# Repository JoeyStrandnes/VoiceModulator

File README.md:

# ESP32-S2 Voice Modulator
This is a work in progress ESP32-S2 Voice Modulator 

### Project goals

- [ ] Capture audio from onboard microphone or headsets.
- [ ] Output audio to a phone or computer by emulating an electret microphone.
- [ ] Modify captured audio in "real" time.

## Schematic and analog functionality

##### It is still a work in progress, use with discretion!

### Microphone amplifier

<iframe width="800" height="600" src="https://www.multisim.com/content/QH8fA5JWDjDa823kgBHJLT/electretmic-amplifier/open"></iframe>

### Microphone output

<iframe width="800" height="600" src="https://www.multisim.com/content/xYbAdgF2BNmvYUGru4YRbm/dac_to_electret/open"></iframe>

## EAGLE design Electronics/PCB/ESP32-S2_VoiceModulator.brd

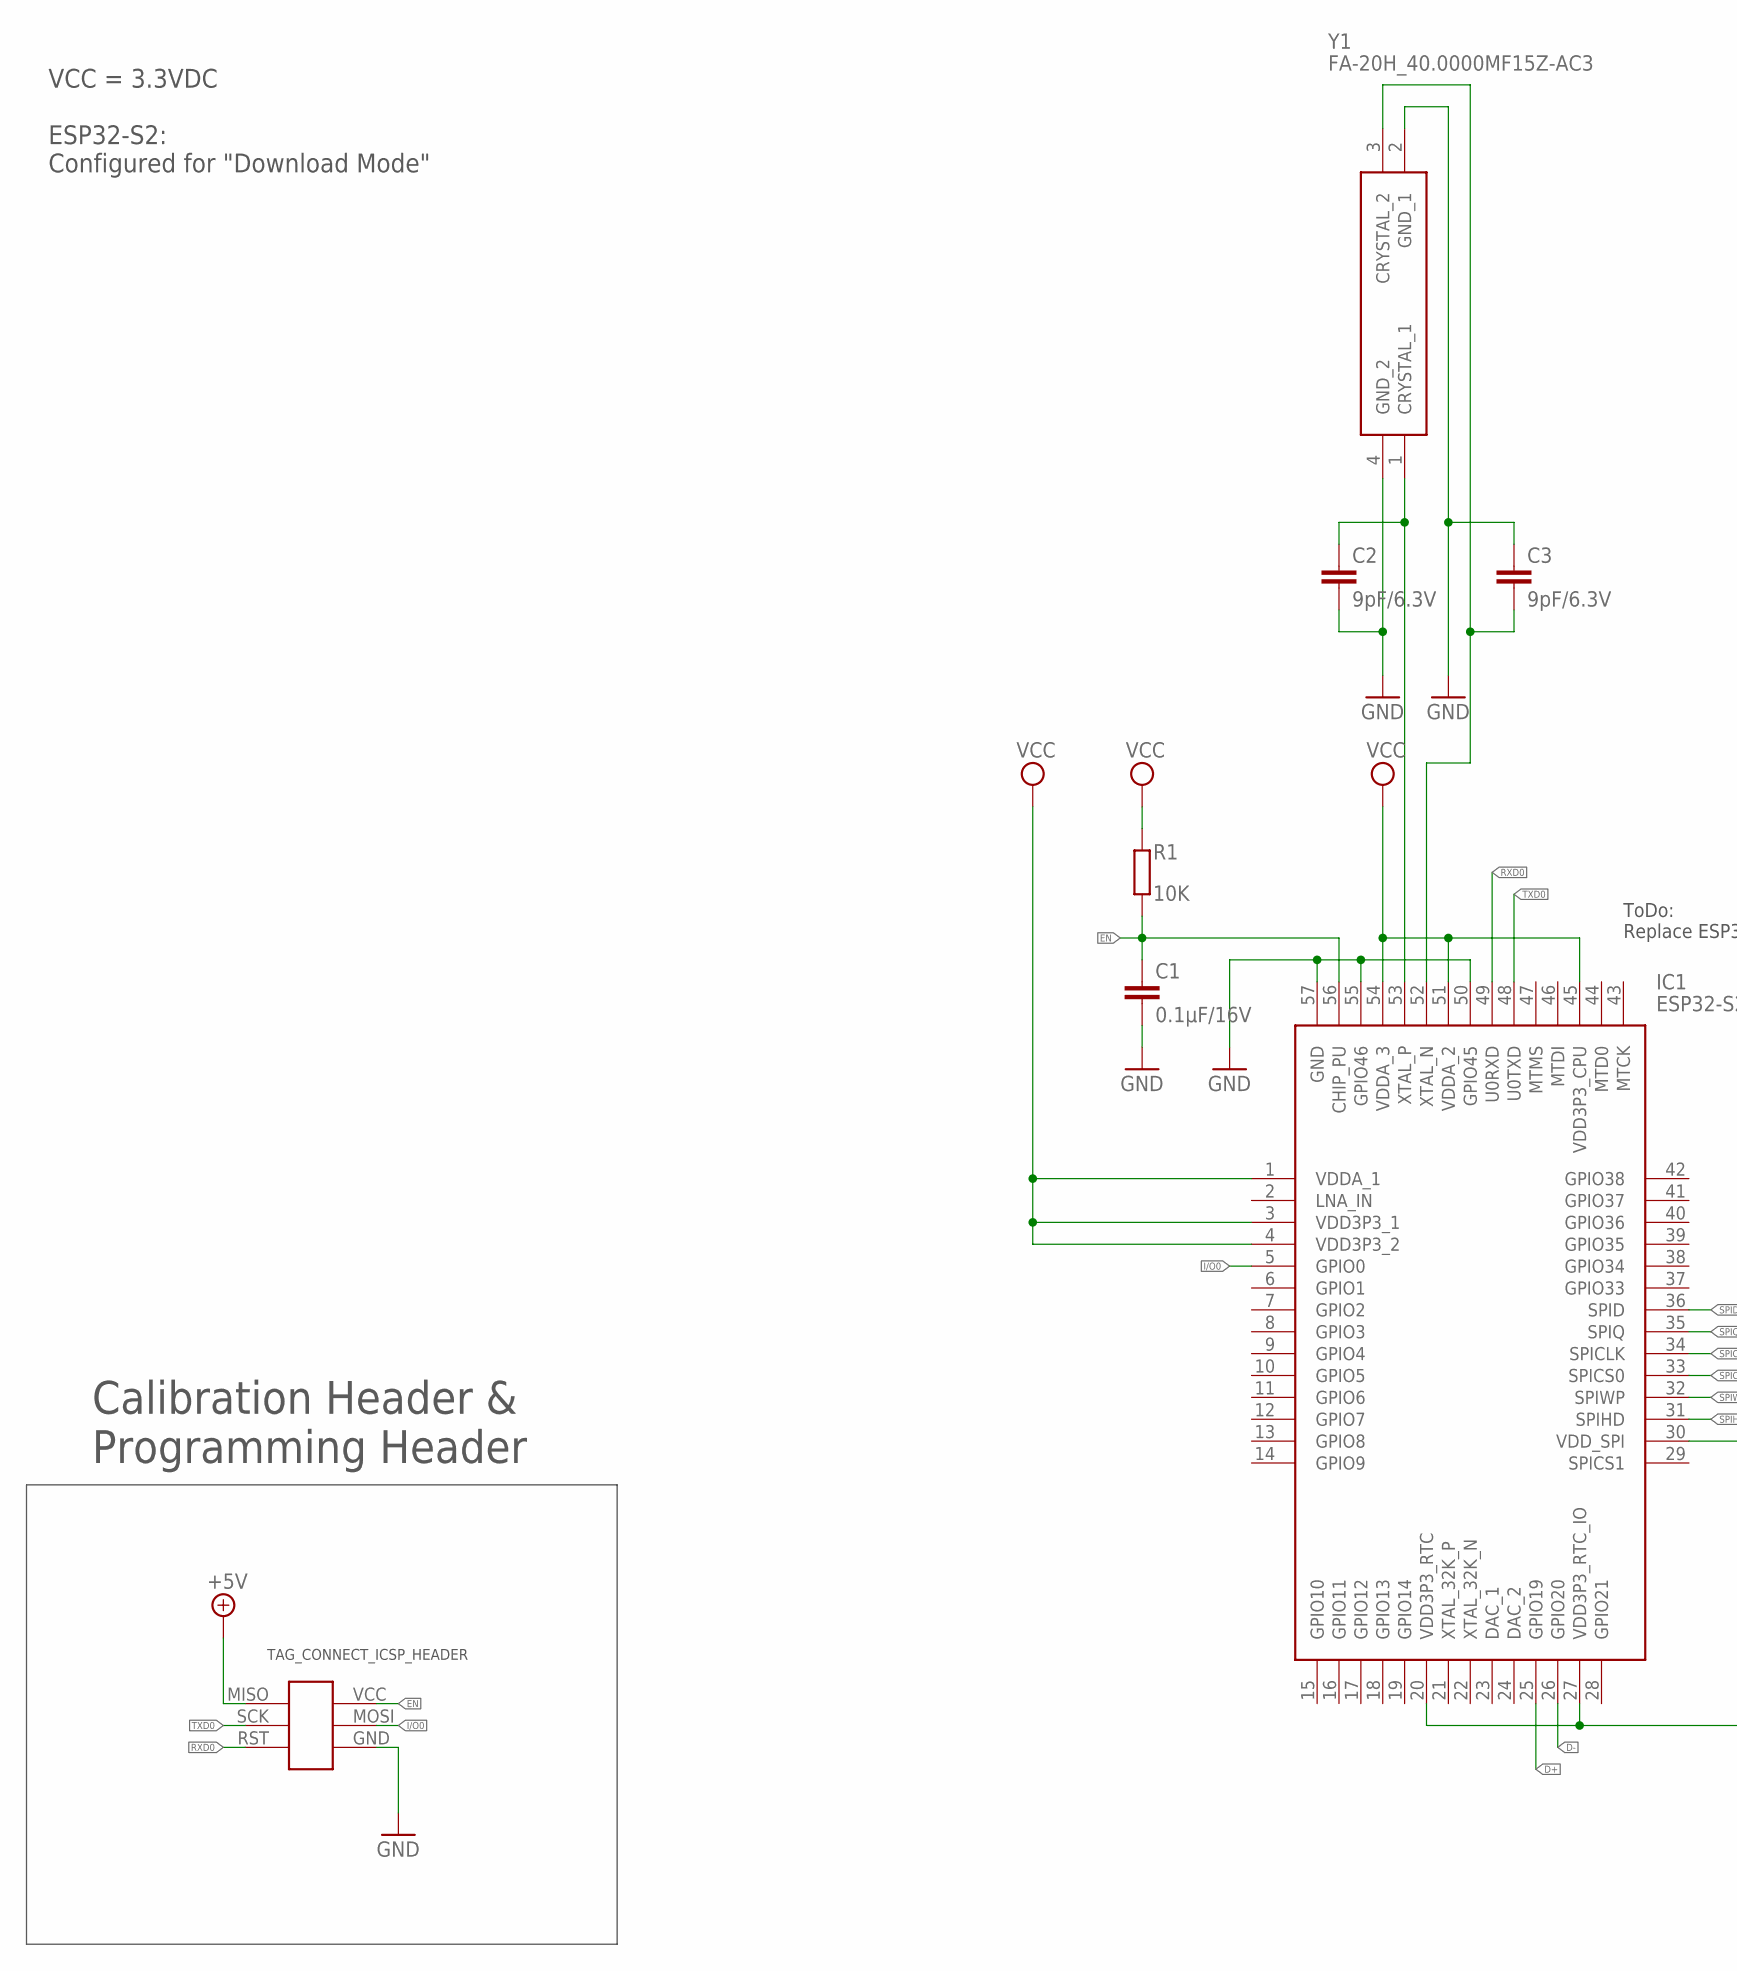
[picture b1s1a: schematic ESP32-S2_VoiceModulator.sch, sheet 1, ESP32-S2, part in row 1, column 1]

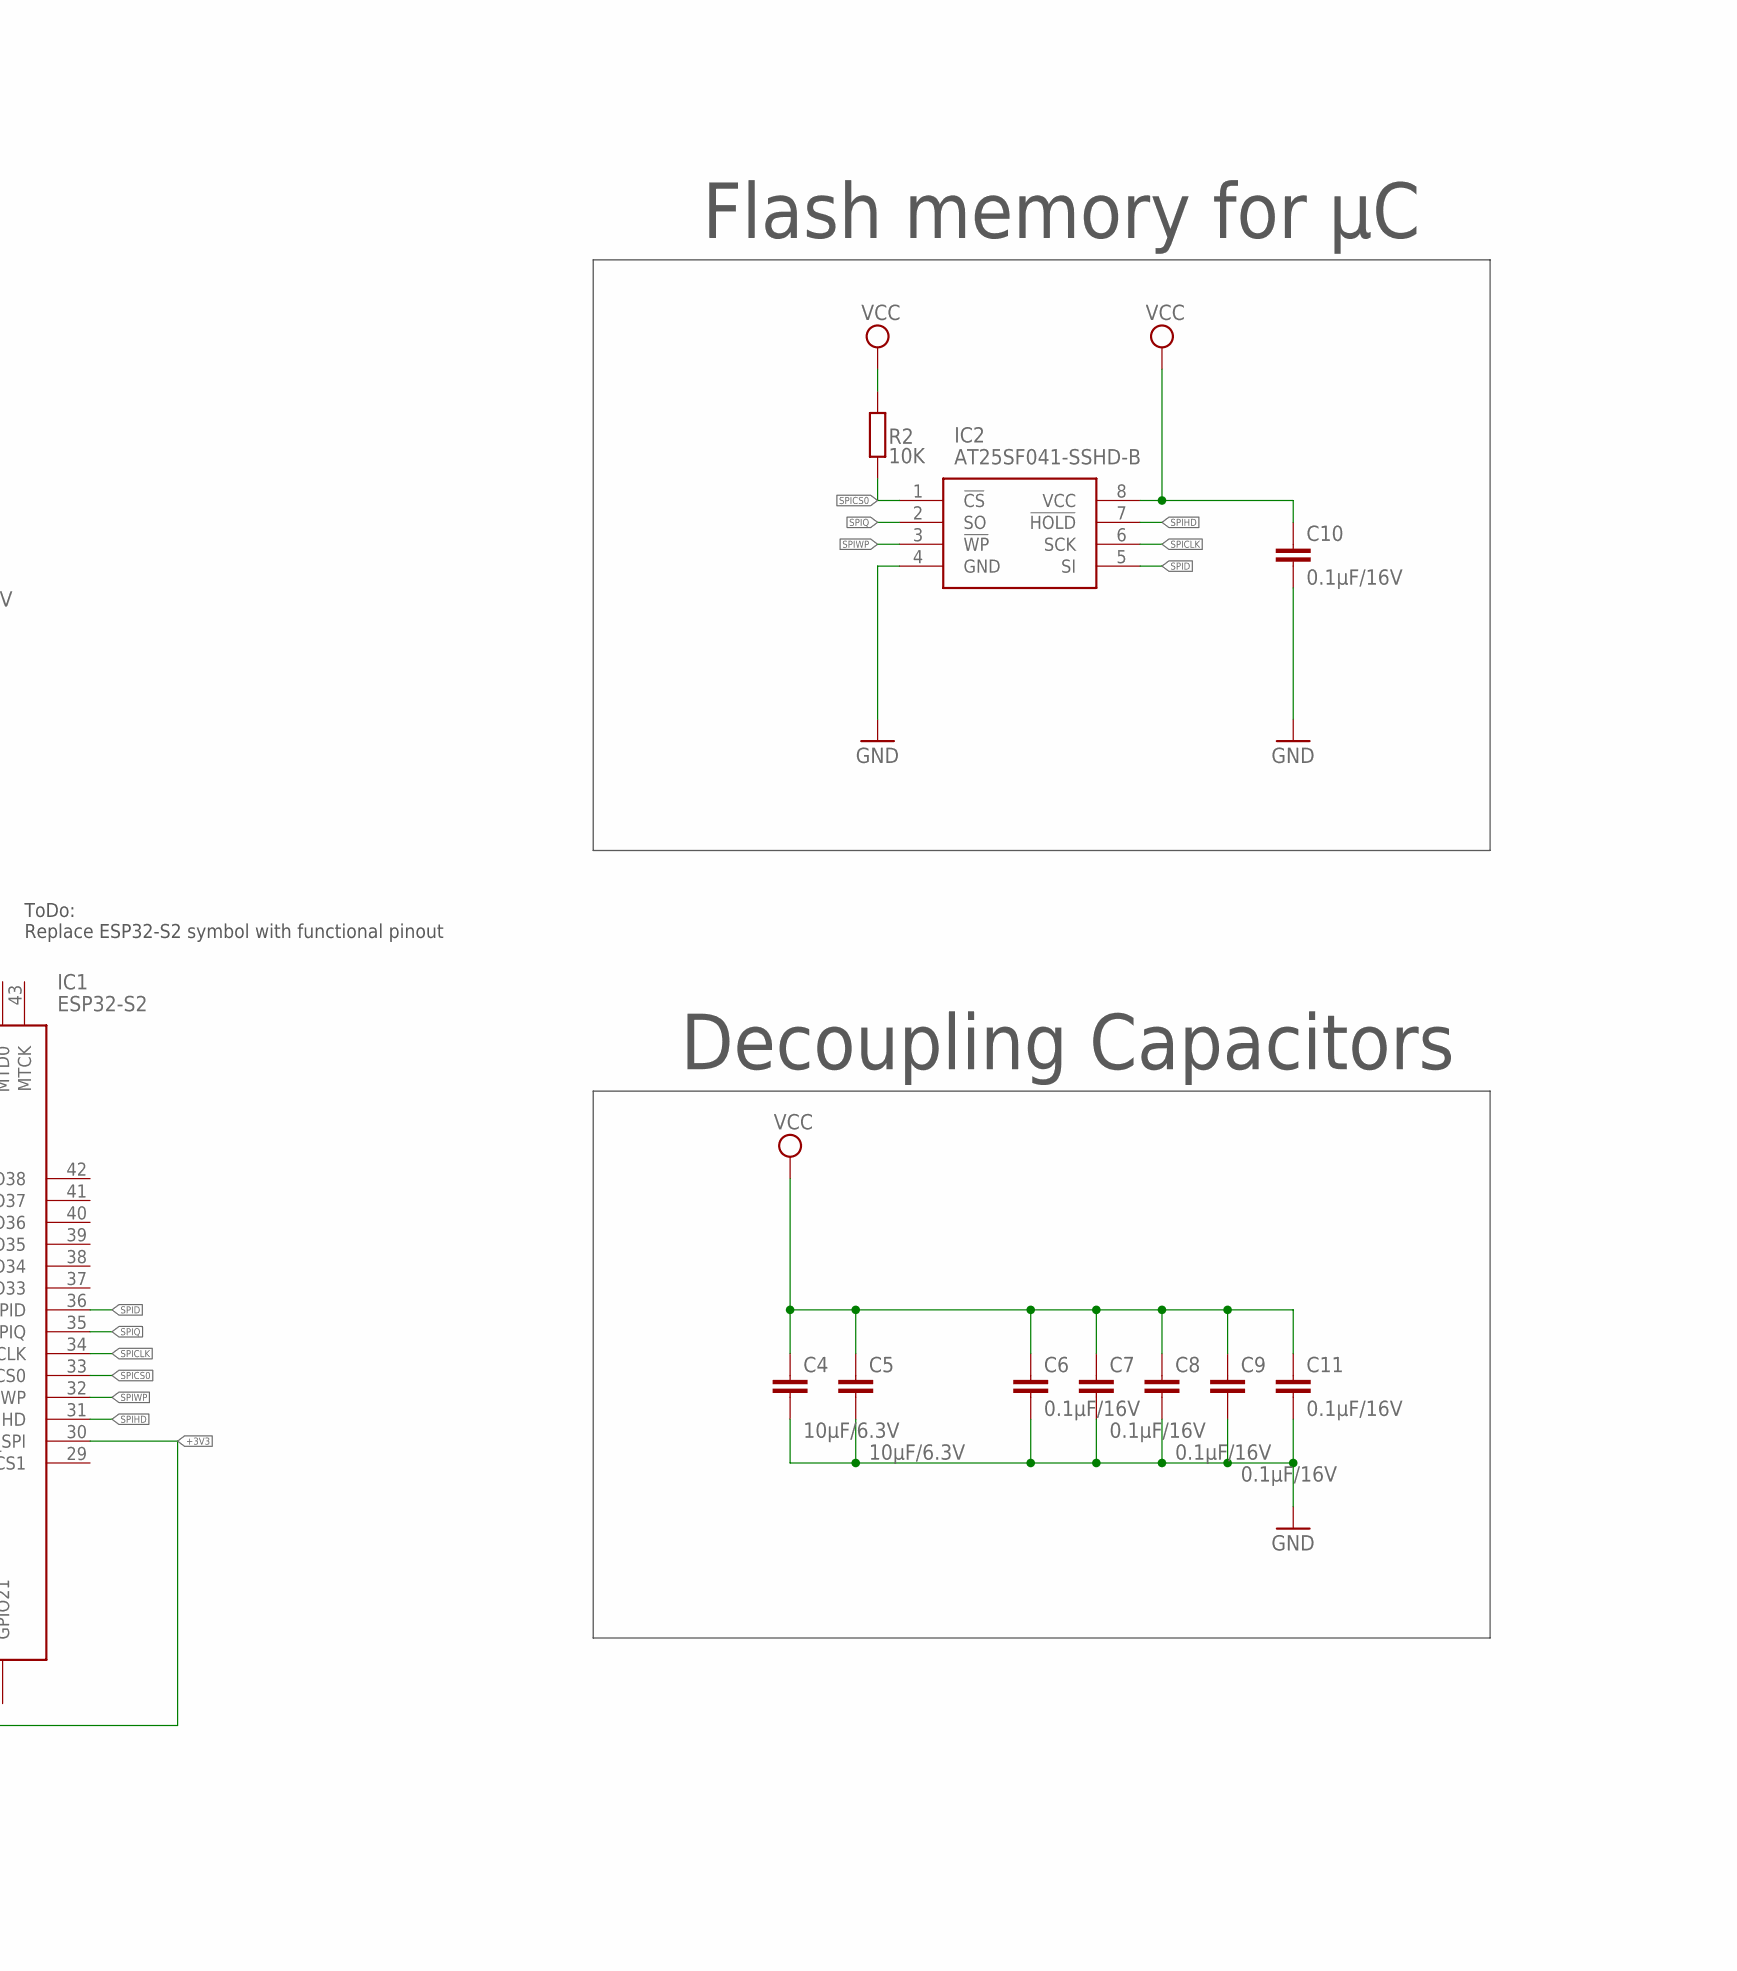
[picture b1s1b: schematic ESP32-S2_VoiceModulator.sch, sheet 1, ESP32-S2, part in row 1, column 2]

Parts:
C1, C6, C7, C8, C9, C10, C11: 0.1µF/16V; C0402
C2, C3: 9pF/6.3V; C0603
C4, C5: 10µF/6.3V; C0603
IC1: ESP32-S2; QFN40P700X700X90-57N
IC2: AT25SF041-SSHD-B; SOIC127P600X175-8N
R1, R2: 10K; R0603
TAG_CONNECT_ICSP_HEADER: TAG-CONNECT_PADS
Y1: FA-20H_40.0000MF15Z-AC3; FA20H160000MF12ZAC3

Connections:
+3V3: IC1.20 (VDD3P3_RTC), IC1.27 (VDD3P3_RTC_IO), IC1.30 (VDD_SPI)
+5V: TAG_CONNECT_ICSP_HEADER.MISO; also elsewhere on the board
D+: IC1.25 (GPIO19); also elsewhere on the board
D-: IC1.26 (GPIO20); also elsewhere on the board
EN: C1.1, IC1.56 (CHIP_PU), R1.1, TAG_CONNECT_ICSP_HEADER.VCC
GND: C1.2, C2.2, C3.1, C4.2, C5.2, C6.2, C7.2, C8.2, C9.2, C10.2, C11.2, IC1.50 (GPIO45), IC1.55 (GPIO46), IC1.57 (GND), IC2.4 (GND), TAG_CONNECT_ICSP_HEADER.GND, Y1.2 (GND_1), Y1.4 (GND_2); also elsewhere on the board
I/O0: IC1.5 (GPIO0), TAG_CONNECT_ICSP_HEADER.MOSI
unnamed: C2.1, IC1.53 (XTAL_P), Y1.1 (CRYSTAL_1)
unnamed: C3.2, IC1.52 (XTAL_N), Y1.3 (CRYSTAL_2)
RXD0: IC1.49 (U0RXD), TAG_CONNECT_ICSP_HEADER.RST
SPICLK: IC1.34 (SPICLK), IC2.6 (SCK)
SPICS0: IC1.33 (SPICS0), IC2.1 (!CS), R2.1
SPID: IC1.36 (SPID), IC2.5 (SI)
SPIHD: IC1.31 (SPIHD), IC2.7 (!HOLD)
SPIQ: IC1.35 (SPIQ), IC2.2 (SO)
SPIWP: IC1.32 (SPIWP), IC2.3 (!WP)
TXD0: IC1.48 (U0TXD), TAG_CONNECT_ICSP_HEADER.SCK
VCC: C4.1, C5.1, C6.1, C7.1, C8.1, C9.1, C10.1, C11.1, IC1.1 (VDDA_1), IC1.3 (VDD3P3_1), IC1.4 (VDD3P3_2), IC1.45 (VDD3P3_CPU), IC1.51 (VDDA_2), IC1.54 (VDDA_3), IC2.8 (VCC), R1.2, R2.2; also elsewhere on the board

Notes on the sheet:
Flash memory for µC
Decoupling Capacitors
VCC = 3.3VDC ESP32-S2: Configured for "Download Mode"
Calibration Header & Programming Header
ToDo: Replace ESP32-S2 symbol with functional pinout

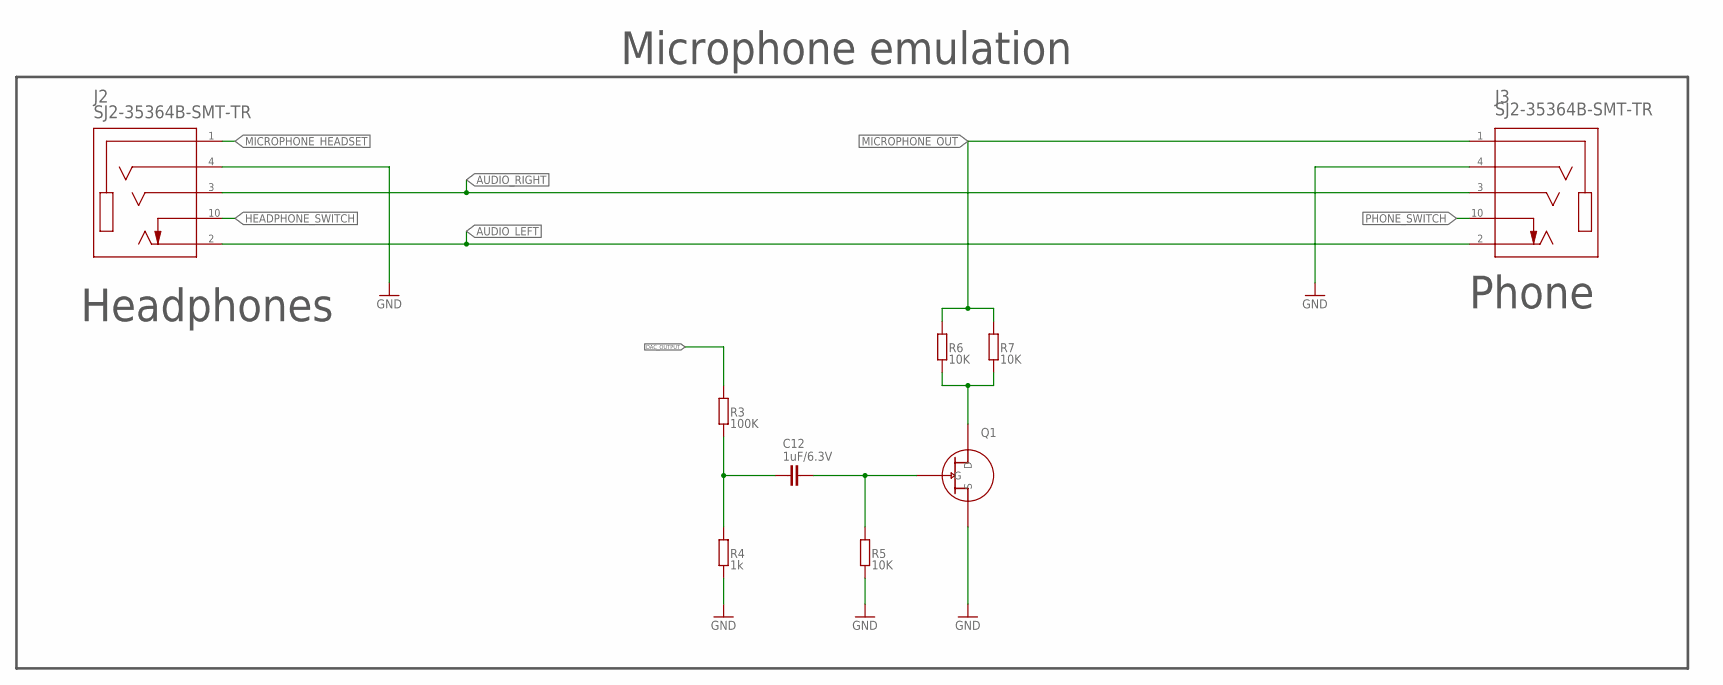
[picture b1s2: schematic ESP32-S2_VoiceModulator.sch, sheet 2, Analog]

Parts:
C12: 1uF/6.3V; C0603
J2, J3: SJ2-35364B-SMT-TR
Q1: CPH3910; SOT-23-3
R3: 100K; R0603
R4: 1k; R0603
R5, R6, R7: 10K; R0603

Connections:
AUDIO_LEFT: J2.2, J3.2
AUDIO_RIGHT: J2.3, J3.3
DAC_OUTPUT: R3.2
GND: J2.4, J3.4, Q1.P$1 (S), R4.1, R5.2; also elsewhere on the board
HEADPHONE_SWITCH: J2.10
MICROPHONE_HEADSET: J2.1; also elsewhere on the board
MICROPHONE_OUT: J3.1, R6.1, R7.2
unnamed: C12.2, Q1.P$3 (G), R5.1
unnamed: C12.1, R3.1, R4.2
unnamed: Q1.P$2 (D), R6.2, R7.1
PHONE_SWITCH: J3.10

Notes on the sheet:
Headphones
Phone
Microphone emulation

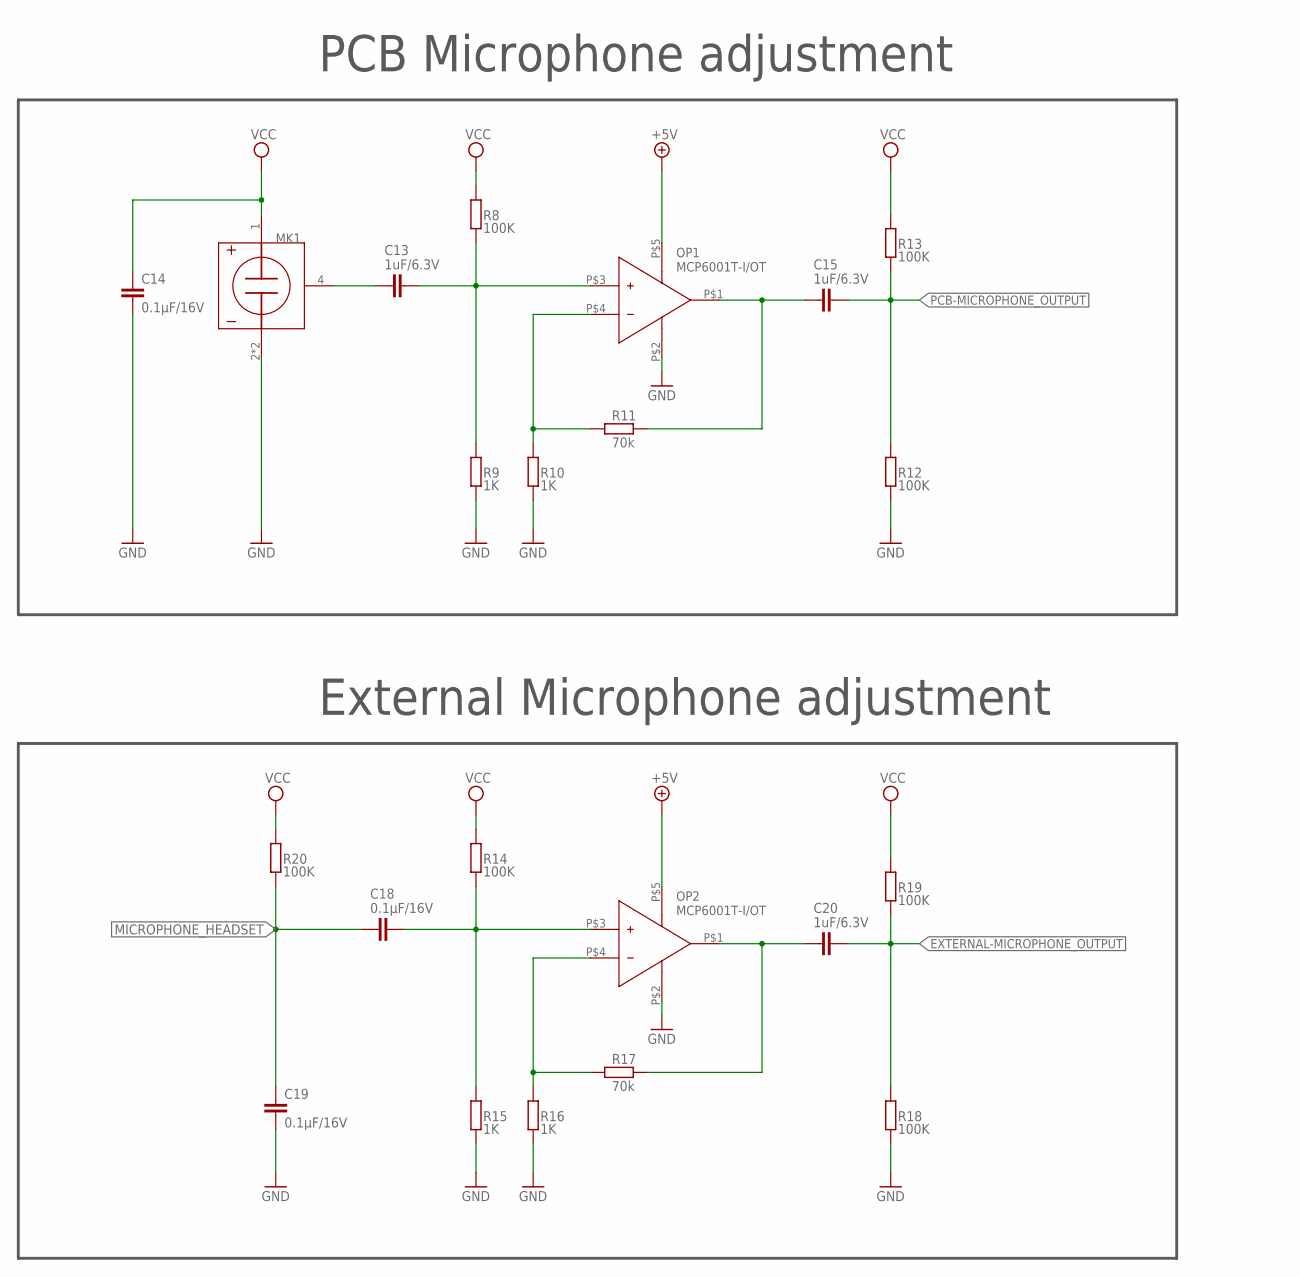
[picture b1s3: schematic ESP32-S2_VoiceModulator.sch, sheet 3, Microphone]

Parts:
C13, C15, C20: 1uF/6.3V; C0603
C14, C19: 0.1µF/16V; C0402
C18: 0.1µF/16V; C0603
MK1: WMM7022AT0
OP1, OP2: MCP6001T-I/OT; SOT-23-5
R8, R12, R13, R14, R18, R19, R20: 100K; R0603
R9, R10, R15, R16: 1K; R0603
R11, R17: 70k; R0603

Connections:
+5V: OP1.P$5 (VDD), OP2.P$5 (VDD); also elsewhere on the board
EXTERNAL-MICROPHONE_OUTPUT: C20.2, R18.2, R19.1
GND: C14.2, C19.2, MK1.2 (GND), MK1.3 (GND), OP1.P$2 (VSS), OP2.P$2 (VSS), R9.1, R10.1, R12.1, R15.1, R16.1, R18.1; also elsewhere on the board
MICROPHONE_HEADSET: C18.1, C19.1, R20.1; also elsewhere on the board
unnamed: C13.2, OP1.P$3 (V+), R8.1, R9.2
unnamed: C13.1, MK1.4 (OUT)
unnamed: OP1.P$4 (V-), R10.2, R11.2
unnamed: C15.1, OP1.P$1 (VOUT), R11.1
unnamed: C18.2, OP2.P$3 (V+), R14.1, R15.2
unnamed: OP2.P$4 (V-), R16.2, R17.2
unnamed: C20.1, OP2.P$1 (VOUT), R17.1
PCB-MICROPHONE_OUTPUT: C15.2, R12.2, R13.1
VCC: C14.1, MK1.1 (VDD), R8.2, R13.2, R14.2, R19.2, R20.2; also elsewhere on the board

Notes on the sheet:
PCB Microphone adjustment
External Microphone adjustment

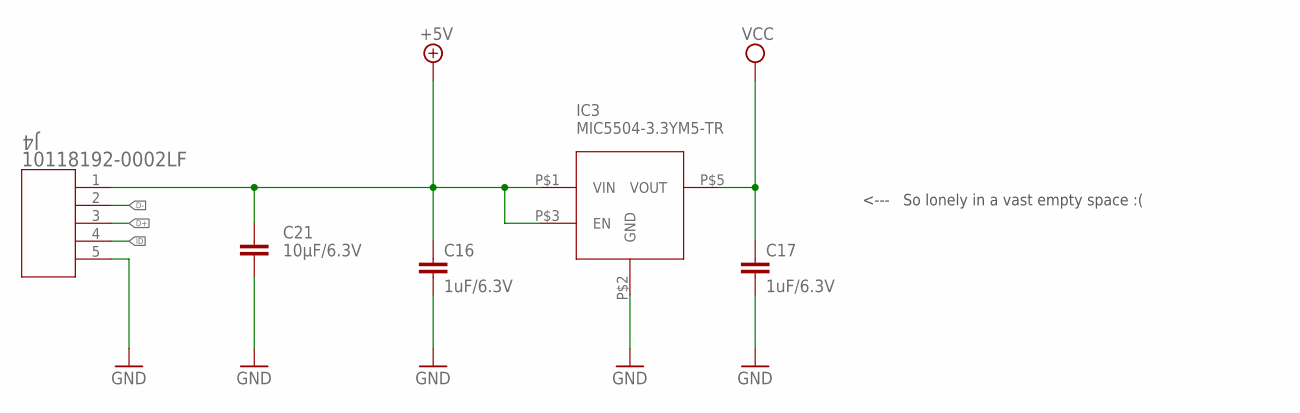
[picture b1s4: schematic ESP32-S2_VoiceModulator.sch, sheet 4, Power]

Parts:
C16, C17: 1uF/6.3V; C0603
C21: 10µF/6.3V; C0603
IC3: MIC5504-3.3YM5-TR; SOT-23-5
J4: 10118192-0002LF; CONN_10118192-0002LF_AMP

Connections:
+5V: C16.1, C21.1, IC3.P$1 (VIN), IC3.P$3 (EN), J4.1; also elsewhere on the board
D+: J4.3; also elsewhere on the board
D-: J4.2; also elsewhere on the board
GND: C16.2, C17.2, C21.2, IC3.P$2 (GND), J4.5; also elsewhere on the board
ID: J4.4
VCC: C17.1, IC3.P$5 (VOUT); also elsewhere on the board

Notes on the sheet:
<--- So lonely in a vast empty space :(

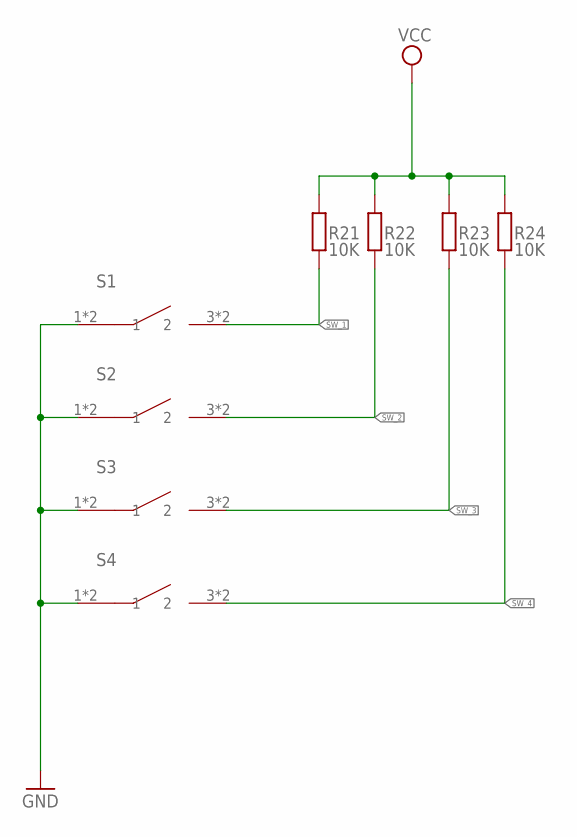
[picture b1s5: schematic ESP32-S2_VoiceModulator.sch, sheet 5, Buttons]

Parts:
R21, R22, R23, R24: 10K; R0603
S1, S2, S3, S4: PTS647SK70SMTR2LFS; PTS647SKXXSMTR2LFS

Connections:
GND: S1.1, S1.2 (1), S2.1, S2.2 (1), S3.1, S3.2 (1), S4.1, S4.2 (1); also elsewhere on the board
SW_1: R21.2, S1.3 (2), S1.4 (2)
SW_2: R22.2, S2.3 (2), S2.4 (2)
SW_3: R23.2, S3.3 (2), S3.4 (2)
SW_4: R24.2, S4.3 (2), S4.4 (2)
VCC: R21.1, R22.1, R23.1, R24.1; also elsewhere on the board

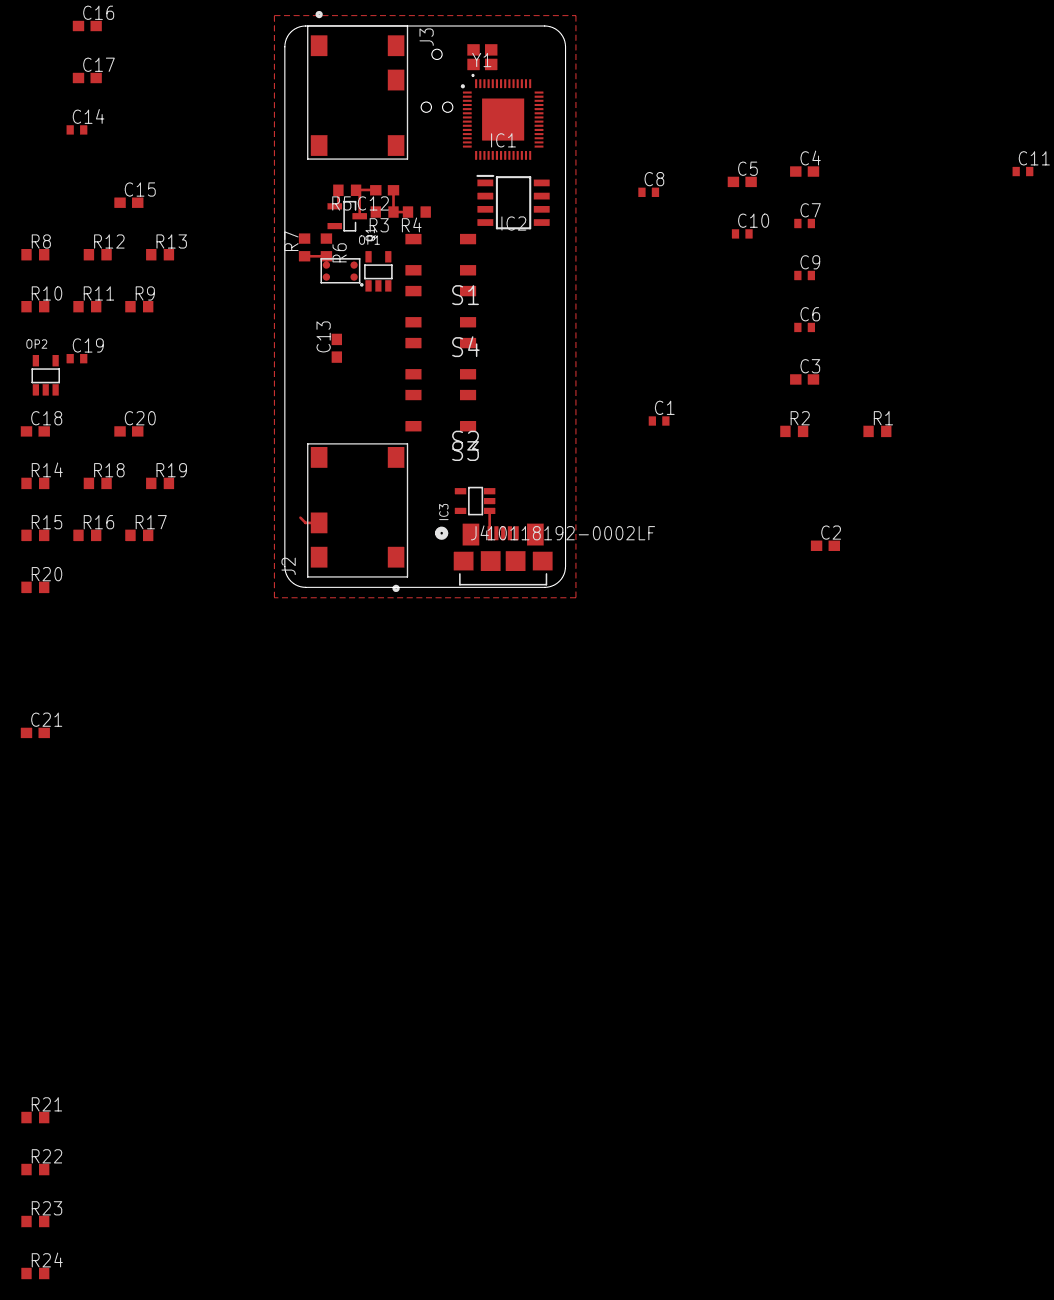
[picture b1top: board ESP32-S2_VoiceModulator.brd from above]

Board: 4 copper layers, 27.0 x 54.0 mm, 61 parts (1 on the bottom side), 38 nets.

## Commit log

2020-11-05 initiated software files
2020-11-05 Removed unnecessary files
2020-11-05 Create LICENSE
2020-11-06 Added preliminary analog output and datasheet
2020-11-06 Added an additional image of characteristics
2020-11-14 Does not work, removed.
2020-11-14 Added working solution for DAC output
2020-11-14 Electronics init
    Added basic schematic for ESP32-S2. Known to work.
2020-11-14 CHanged labelign for VCC/ power
2020-11-16 Added Functional_Overview.drawio
2020-11-16 Added schematic drawing for the microphone emulation and PCB microphone adjustment.
2020-11-16 Added DC/DC
2020-11-16 Moved some files around
2020-11-23 Minor changes to schematic
2020-11-23 Test code
2020-11-23 Created Voice_modular.c
    This file will hold the functions that will alter the incoming voice
2020-11-23 didn't do much
2020-11-23 Minor changes
2020-11-30 Added BitLunis ESP32 ULP audio driver
    Needs to be converted to "Pure" IDF code for the ESP32-S2
2020-11-30 Makefile setup to handle the ULP
    Unable to compile, need to port it to standard IDF
2020-11-30 First test, compiles but no sound...

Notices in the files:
parts and their libraries:
COPYRIGHT: Copyright (C) 2018 Accelerated Designs. All rights reserved
